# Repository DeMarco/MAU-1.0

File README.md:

View this project on [CADLAB.io](https://cadlab.io/project/1285). 

# MAU-1.0
First version of MAU - MicroAltímetro Universal - or "Universal MicroAltimeter" (my Final Year Project)

Folder structure explained: 

Delivery_Clientes --> basically the files that any customer will need to extract data from the altimeter

Delivery_Montagem --> the files needed by whoever is programming the altimeter before delivery o customers

Firmware/MainDev --> source code for the master branch. As of pull request #7, a new feature called "Flex Sampling Rate" is introduced in the master branch, but not yet tested in any real life rocket. Also several minor improvements to the main source code were added, such as better variable names and better comments in English.

Firmware/PrototypeOne --> This folder contains a preserved copy of the "classic" source code as of end of 2018, before the introduction of "Flex Sampling Rate". "P1V16.c" and "definesV16.h" represent the currently commercialized version of the firmware!

Firmware/Tests --> "scratch pad" projects just to test coding ideas

GraphGenerator/MainDev --> source code for the C app that bridges the communication between the altimeter via "USBasp" programmer/reader and a windows PC. It also generates the necessary txt files needed by Excel file "Leitura Dados De Vôo - V1.1.xlsm" to display the altitude graph.

GraphGenerator/old --> preserved copy of the the old C app and Excel files that are compatible with the "classic" firmware version ("PrototypeOne").

Hardware --> the EAGLE files (.brd and .sch) for the hardware design of both the altimeter and the adapter needed to connect it with the USBasp programmer/reader. These files can be visualized in the linked CADLAB.io repo.

Notes --> random scratch pad files with calculations and annotations

TestesPC --> "scratch pad" projects just to test coding ideas on the PC side

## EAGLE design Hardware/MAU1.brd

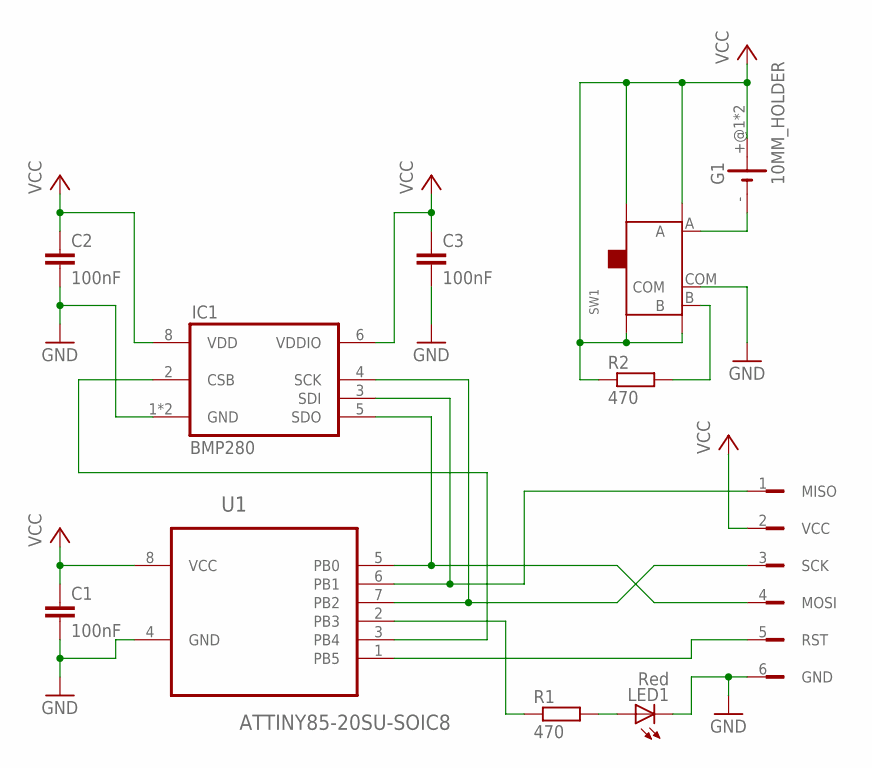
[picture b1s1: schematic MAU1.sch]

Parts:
C1, C2, C3: 100nF; C0603K
G1: 10MM_HOLDER
IC1: BMP280
LED1: Red; KA-3528ASYC
R1, R2: 470; R0603
SW1: SMD-TOGGLE-SWITCH-ON-ON(3+4P-6.7X2.7MM)SLIDE_LATE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; SW7-SMD-6.7X2.6X1.4MM-90D
U1: ATTINY85-20SU-SOIC8; SOIC8-1.27-5.3X5.3MM
U$1: ISP_CONN_6_FDRILL16; ISP_CONN_6_F_DRILL16

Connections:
GND: C1.2, C2.2, C3.2, IC1.1 (GND), IC1.7 (GND), LED1.C, SW1.COM, U1.4 (GND), U$1.6 (GND)
unnamed: G1.-, SW1.A
unnamed: R1.1, U1.2 (PB3)
unnamed: U1.1 (PB5), U$1.5 (RST)
unnamed: LED1.A, R1.2
unnamed: IC1.2 (CSB), U1.3 (PB4)
unnamed: R2.2, SW1.B
unnamed: IC1.4 (SCK), U1.7 (PB2), U$1.3 (SCK)
unnamed: IC1.3 (SDI), U1.6 (PB1), U$1.1 (MISO)
unnamed: IC1.5 (SDO), U1.5 (PB0), U$1.4 (MOSI)
VCC: C1.1, C2.1, C3.1, G1.+@1 (+), G1.+@2 (+), IC1.6 (VDDIO), IC1.8 (VDD), R2.1, SW1.P1 (SS4), SW1.P2 (SS3), SW1.P3 (SS2), SW1.P4 (SS1), U1.8 (VCC), U$1.2 (VCC)

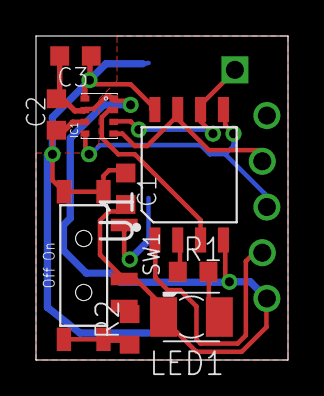
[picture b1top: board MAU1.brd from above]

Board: 2 copper layers, 14.0 x 18.0 mm, 11 parts (0 on the bottom side), 11 nets.

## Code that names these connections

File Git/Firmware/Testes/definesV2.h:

/*
 * defines.h
 *
 * Created: 16/07/2016 20:48:40
 *  Author: DRAYCON
 */ 


#ifndef DEFINES_H_
#define DEFINES_H_

/* General */
#define HIGH	1
#define LOW		0

#define TRUE	1
#define FALSE	0

#define PRESSURE	0
#define TEMPERATURE	1

#define output_high(pin)		PORTB |= _BV(pin)
#define output_low(pin)			PORTB &= ~_BV(pin)


/* CPU frequency */
#define F_CPU 1000000UL


/* Calculate a post scaler for Timer1 */
#define _PS(instant)	(uint16_t)((instant * F_CPU) / TIMER1_FULL_VALUE)


/* ATtiny85 used pins */
#define DI   PB0
#define DO   PB1
#define USCK PB2
#define LED  PB3
#define CSB  PB4


/* BMP280 registers */
#define READ		0x80
#define WRITE		0x7f
#define BLANK		0x00

#define	TEMP_XLSB	0xfc
#define	TEMP_LSB	0xfb
#define	TEMP_MSB	0xfa
#define	PRESS_XLSB	0xf9
#define	PRESS_LSB	0xf8
#define	PRESS_MSB	0xf7

#define	CONFIG		0xf5
#define T_SB2		7
#define T_SB1		6
#define T_SB0		5
#define FILTER2		4
#define FILTER1		3
#define FILTER0		2
#define SPI3W_EN	0

#define	CTRL_MEAS	0xf4
#define OSRS_T2		7
#define OSRS_T1		6
#define OSRS_T0		5
#define OSRS_P2		4
#define OSRS_P1		3
#define OSRS_P0		2
#define MODE1		1
#define MODE0		0

#define	STATUS		0xf3
#define MEASURING	3
#define IM_UPDATE	0

#define	RESET		0xe0
#define RST_BYTE	0xb6

#define	ID			0xd0

//Temperature Oversampling = Ultra Low Power; Pressure Oversampling = Ultra Low Power; Mode = Normal;
//#define BMP280_SETUP_CTRL	_BV(OSRS_T0) | _BV(OSRS_P0) | _BV(MODE1) | _BV(MODE0) //

//Temperature Oversampling = Ultra Low Power; Pressure Oversampling = Ultra Low Power; Mode = Sleep;
#define BMP280_SETUP_CTRL	(_BV(OSRS_T0) | _BV(OSRS_P0))

//Stand by time = 125ms; Filter coeficient = 4;
#define BMP280_SETUP_CONFIG	(_BV(T_SB1) | _BV(FILTER1))

#define BMP280_OSRS_P		(_BV(OSRS_P2) | _BV(OSRS_P1) | _BV(OSRS_P0))

#define BMP280_PRESS_SKIP	~_BV(OSRS_P2) & ~_BV(OSRS_P1) & ~_BV(OSRS_P0)
#define BMP280_PRESS_ULP	_BV(OSRS_P0)
#define BMP280_PRESS_LP		_BV(OSRS_P1)
#define BMP280_PRESS_SR		_BV(OSRS_P1) | _BV(OSRS_P0)
#define BMP280_PRESS_HR		_BV(OSRS_P2)
#define BMP280_PRESS_UHR	_BV(OSRS_P2) | _BV(OSRS_P0)

#define BMP280_OSRS_T		(_BV(OSRS_T2) | _BV(OSRS_T1) | _BV(OSRS_T0))

#define BMP280_TEMP_SKIP	~_BV(OSRS_T2) & ~_BV(OSRS_T1) & ~_BV(OSRS_T0)
#define BMP280_TEMP_ULP		_BV(OSRS_T0)
#define BMP280_TEMP_LP		_BV(OSRS_T1)
#define BMP280_TEMP_SR		_BV(OSRS_T1) | _BV(OSRS_T0)
#define BMP280_TEMP_HR		_BV(OSRS_T2)
#define BMP280_TEMP_UHR		_BV(OSRS_T2) | _BV(OSRS_T0)

#define BMP280_MODE_SLEEP	~_BV(MODE1) & ~_BV(MODE0)
#define BMP280_MODE_FORCED	_BV(MODE0)
#define BMP280_MODE_NORMAL	_BV(MODE1) | _BV(MODE0)

#define PRESSURE_ONLY		0xf7, 3
#define TEMPERATURE_ONLY	0xfa, 3
#define PRESS_AND_TEMP		0xf7, 6


/* Timer Settings */
#define TIMER1_FULL_VALUE	256UL

#define MAX_FLIGHT_TIME				44 //in seconds
#define BMP280_MAX_CYCLE_COUNT		MAX_FLIGHT_TIME / MEASUREMENT_PERIOD

#define MEASUREMENT_PERIOD		0.192 //in seconds
#define MEASUREMENT_INSTANT		0.192
#define READOUT_INSTANT			0.142
#define EEPROM_WRITE_INSTANT	0.132
#define LED_ON_INSTANT			0.082
#define LED_OFF_INSTANT			0.072

#define POST_SCALER_MEASUREMENT		_PS(MEASUREMENT_INSTANT)
#define POST_SCALER_READOUT			_PS(READOUT_INSTANT)
#define POST_SCALER_WRITE_EEPROM	_PS(EEPROM_WRITE_INSTANT)
#define POST_SCALER_LED_ON			_PS(LED_ON_INSTANT)
#define POST_SCALER_LED_OFF			_PS(LED_OFF_INSTANT)


/* EEPROM settings */
#define EEPROM_ADDRESS_LAST		510
#define EEPROM_ADDRESS_MAX		EEPROM_ADDRESS_LAST - 10

#endif /* DEFINES_H_ */

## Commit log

2018-07-29 Commiting project relevant files
2018-07-29 Moved to correct folder in PC
2018-08-07 Testing file change with Atom
2018-08-07 Another test
2018-08-17 Moved stuff to Notes folder
2018-09-09 Added EAGLE to gitignore
2018-09-09 Brought HW project to main repo
2018-09-09 Backlink to CADLAB.io has been added.
2019-02-02 Prepared MainDev project for continuing development. PrototypeOne is now a frozen version of the firmware of MAU-1.0 currently released to production.
2019-02-02 Placing fluxogram files at MainDev, PrototypeOne and GraphGenerator folders
2019-02-03 Translated firmware comments and flowcharts
2019-02-03 Deleted old portuguese firmware flowcharts
2019-02-04 Update MAIN FLOWCHART.html
    Included step for saving barometers calibration constants before auto shut down.
2019-02-10 Fixed bugs caused by the renaming of def constants in the atmospheric model header. Added batches to MainDev folder for quickly flashing the firmware and erasing the EEPROM.
2019-02-10 Added comment questioning the zeroing (in meters) of the first sample in the NVM.
2019-02-20 Placed comment explaining how the altimeter stops recording once NVM is full.
2019-03-03 Updated Main Flowchart with method to calculate Initial Ground Pressure and Landing Detection based on 20 raw pressure samples variance.
2019-03-03 Fixed landing detection condition to be just "variance < value", since variance can never be negative.
2019-03-03 Strategy for parachute descent detection and sampling rate reduction.
2019-03-03 Preparations for flexible sampling rate implementation. TESTS OK.
2019-03-03 Average pressure change rate based variance calculation is ready.
2019-03-09 Pressure change rate + its variance as conditions for landing detection. In the current state, the program works fine for tests in the glass jar (thus, expected to work for short quick flights), but 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
2019-03-09 Step to record in NVM sample index that marks the sample rate reduction.
2019-03-09 Fixed missing "false" flow indicators.
2019-03-09 Reorganized EEPROM addresses in test mode to not disrupt the Excel.
2019-03-09 Remaining flight time prediction working. Ready for simulated profiles.
2019-03-09 Worked with several simulated flight samples set. It is possible to select FLIGHT_SIM mode and several flight profile headers that replace the readings from the actual barometer.
2019-03-10 Removed useless cycles number limiter related variables and some trash.
2019-03-10 Merged calls to rawdata_readout_cycle to one call only. Process type is switched from DETECT_ASCENT to DETECT_LANDING inside of DETECT_ASCENT high variance detected condition. Removed other useless s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
2019-03-10 Changed flow section naming comments
2019-03-10 VERSION FOR TEST IN REAL ROCKET.
2019-03-10 Minor comment fixed.
2019-03-10 Wrapped the call to report_apogee in #ifnotdef TEST_MODE and FLIGHT_SIM
2019-03-10 VERSION READY FOR TEST IN ROCKET.
    Set first NVM position to receive a sample at address 0x08 right from
    the call to rawdata_readout_cycle() from main().
2019-03-11 Finished updates to support the new MAU 1.1 firmware:
    1) Adjusted Flight Profiles to match transition between sampling rates.
    2) Created folder MainDev for the GraphGenerator and updated the program
    to support timestamps generation.
    3) Updated the Excel sheet to support timestamps and adaptive chart
    lenght.
    4) Moved old GraphGenerator and Excel sheet implementations to folder
2019-07-12 Adding the license file
2019-07-12 Adding GNU GPL v3.0 license to the branch
2019-07-12 Included license notice in the README
2019-07-12 Flex Sampling Rate new feature merge (#7)
    * Strategy for parachute descent detection and sampling rate reduction.
    * Preparations for flexible sampling rate implementation. TESTS OK.
    * Average pressure change rate based variance calculation is ready.
    * Pressure change rate + its variance as conditions for landing detection. In the current state, the program works fine for tests in the glass jar (thus, expected to work for short quick flights), bu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
    * Step to record in NVM sample index that marks the sample rate reduction.
    * Fixed missing "false" flow indicators.
2023-03-06 Update README.md
    Adding folder strcture explanation to README
2024-08-25 Updated Microchip Studio stuff
2025-01-20 Added Gerber files and some example images
